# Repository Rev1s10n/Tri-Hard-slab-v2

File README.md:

# Tri-Hard slab v2
## **English | [繁體中文](README_zh-TW.md)**
Slim all button controller powered by [GP2040-CE](https://gp2040-ce.info/) firmware (v0.7.5), with custom 15 buttons layout mainly for Street Fighter 6 and upcoming games that may support additional keybinding.

Mainly inspired by [Egg On Rice Controller](https://github.com/b1nc/Egg-On-Rice-Controller) by [b1nc](https://github.com/b1nc), [Mille-feuille](https://pomegd.booth.pm/items/2685530) by [ぽめ](https://twitter.com/pomegd) and [BridgeBoard](https://bridgeshop.booth.pm/items/4869470) by [立川 Bridge](https://twitter.com/GBB_tachikawa).

The design is heavily based on [flatbox](https://github.com/jfedor2/flatbox) rev4 by [jfdeor2](https://github.com/jfedor2) and [USB Passthrough Board](https://github.com/OpenStickCommunity/Hardware/tree/main/USB%20Passthrough%20Board) by [TheTrain](https://github.com/TheTrainGoes) and [Lucipher](https://github.com/arntsonl), which is licensed under [CC BY 4.0](https://creativecommons.org/licenses/by/4.0/).

## Key features and specs
- Dimensions: 270x157x15.6mm, with additional foam pad (for better grip on lap) at the bottom added 4mm so the total height is around 20mm.
- Weights: around 800g.
- Laser-cut arcylic sheets for enclosure, with strap holes on the top.
- Main key switches: Kailh low profile Choc v2 red, with hot swap sockets and Punk Workshop's key caps.
- 1 RGB LED for each key, with additional 4 RGB LEDs for player number indication (XInput only).
- USB Type-C connector, and additional USB Type-A for PS passthrough authentication.
- 1.3 inches OLED display for various info.
- 3 slide switches on the right side for focus mode, SOCD mode and LS / RS / DP change in real-time.

Some close up photo for each feature:

_Main circuit is heavily based on flatbox with some components replaced due to parts shortage_

_3 tactile switches for your daily stuff and the display on the top left, there's additional slide switch for display pin switch (GND / VCC)_

_All slide switches on the right hand side, they sit flush with the enclosure but still can be reach easily_

_It's nice to have but it's only for XInput mode_

_PS5 ready, I guess_

## Production files

_A quick 3D render I did while waiting for acrylic layers_

You can simply download all production files via Hardware files folder, and utilize services like JLCPCB (which is what I did in this case) to order the board. As for the arcrylic layers, use all dxf files and order 1 for each with the exact height mentioned on the filename for optimal result.
To refine it further, send the step files to vendor to ask them to do either fillet (round corner) or chamfer for at least the top layer.

## Source files
The Tri-Hard slab v2 is made with Autodesk Fusion 360 and KiCad 7.0.
Everything is under Source files, include a rough Fusion 360 sketch which is the base of all laser-cut dxf files, step file and for KiCad to align things up. There's additional footprints for some parts that is somewhat interchangeable, but you may need to put extra works like rewire some traces or edit edge cuts.

## Assemble and settings

_Layer indication for acrylic_

Besides the PCB and acrylics, you need to order some additional things for the build:
- Kailh low profile switches, obviously, depends on your keycaps, I use v2 specifically as I want to use Punk Workshop's keycap.
- 15 Kailh low profile hotswap socket (for PG1350, which is compatible with PG1353).
- A 1.3 inches OLED display, which you can find pretty much everywhere, usually it's SH1106 driver, make sure to check the pin order and set the pins accordingly with the slide switch next to it.
- 6 M6 sex bolts / Chicago screws with around 14mm length to secure the whole things.

I've compiled a custom firmware with custom button layout for the OLED display and assigned all the GPIO for each keys and switches, which you can find under Firmware and setting files folder, there's a backup setting files as well with some additional RGB LED setting. Here's some GPIO pin mapping info for reference:
|Keys|GPIO|
|-|-|
|Up|14|
|Down|12|
|Left|11|
|Right|13|
|B1/1K/A/Circle|18|
|B2/2K/B/Cross|19|
|B3/1P/X/Square|15|
|B4/2P/Y/Triangle|16|
|L1/4P/LB|21|
|R1/3P/RB|17|
|L2/4K/LT|22|
|R2/3K/RT|20|
|S1/Select/Back|6|
|S2/Start|8|
|L3/LS|10|
|R3/RS|9|
|A1/Home/Guide|7|
|A2/Touch|24|

Additionally here's the GPIO and some other settings for other features and addons:
|Features|GPIO and index|
|-|-|
|RGB LED Data Pin|3|
|Player LEDs|starting from 15 to 18|
|Display SDA|4|
|Display SCL|5|
|Joystick Selection Slider Pin 1|26|
|Joystick Selection Slider Pin 2|25|
|SOCD Cleaning Mode Selection Slider Pin 1|28|
|SOCD Cleaning Mode Selection Slider Pin 2|27|
|PS Passthrough D+|1|
|PS Passthrough D-|2 (automactically selected)|
|Focus Mode Pin|29|

When it's done, to access web configurator again, just hold S2/Start (GPIO8) which is located on the top left and connect to the PC.

## Custom artwork

You can download the PSD file and dxf drawing reference in Custom artwork template folder for top panel.
Print it out and insert the artwork between 01 and 02 acrylic layers.

## Attribution
You're free to use this design as long as you credit to this page.
[Licensed under CC BY 4.0](https://creativecommons.org/licenses/by/4.0/)

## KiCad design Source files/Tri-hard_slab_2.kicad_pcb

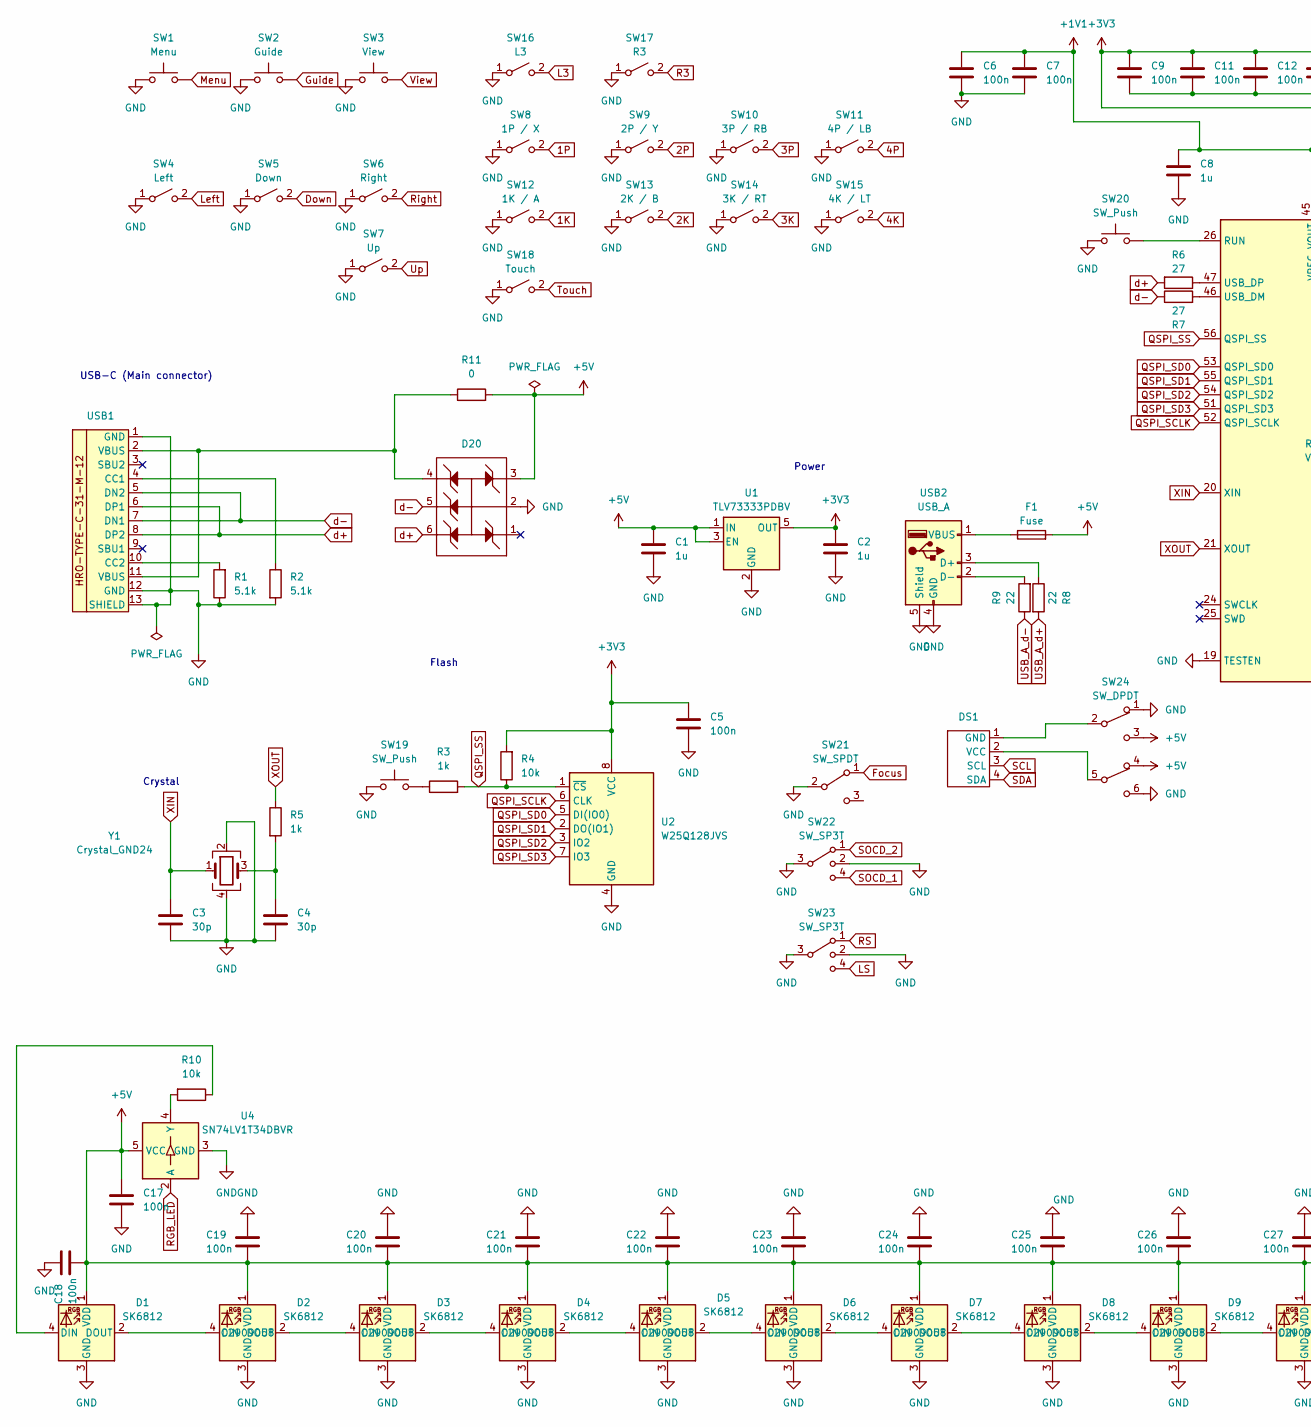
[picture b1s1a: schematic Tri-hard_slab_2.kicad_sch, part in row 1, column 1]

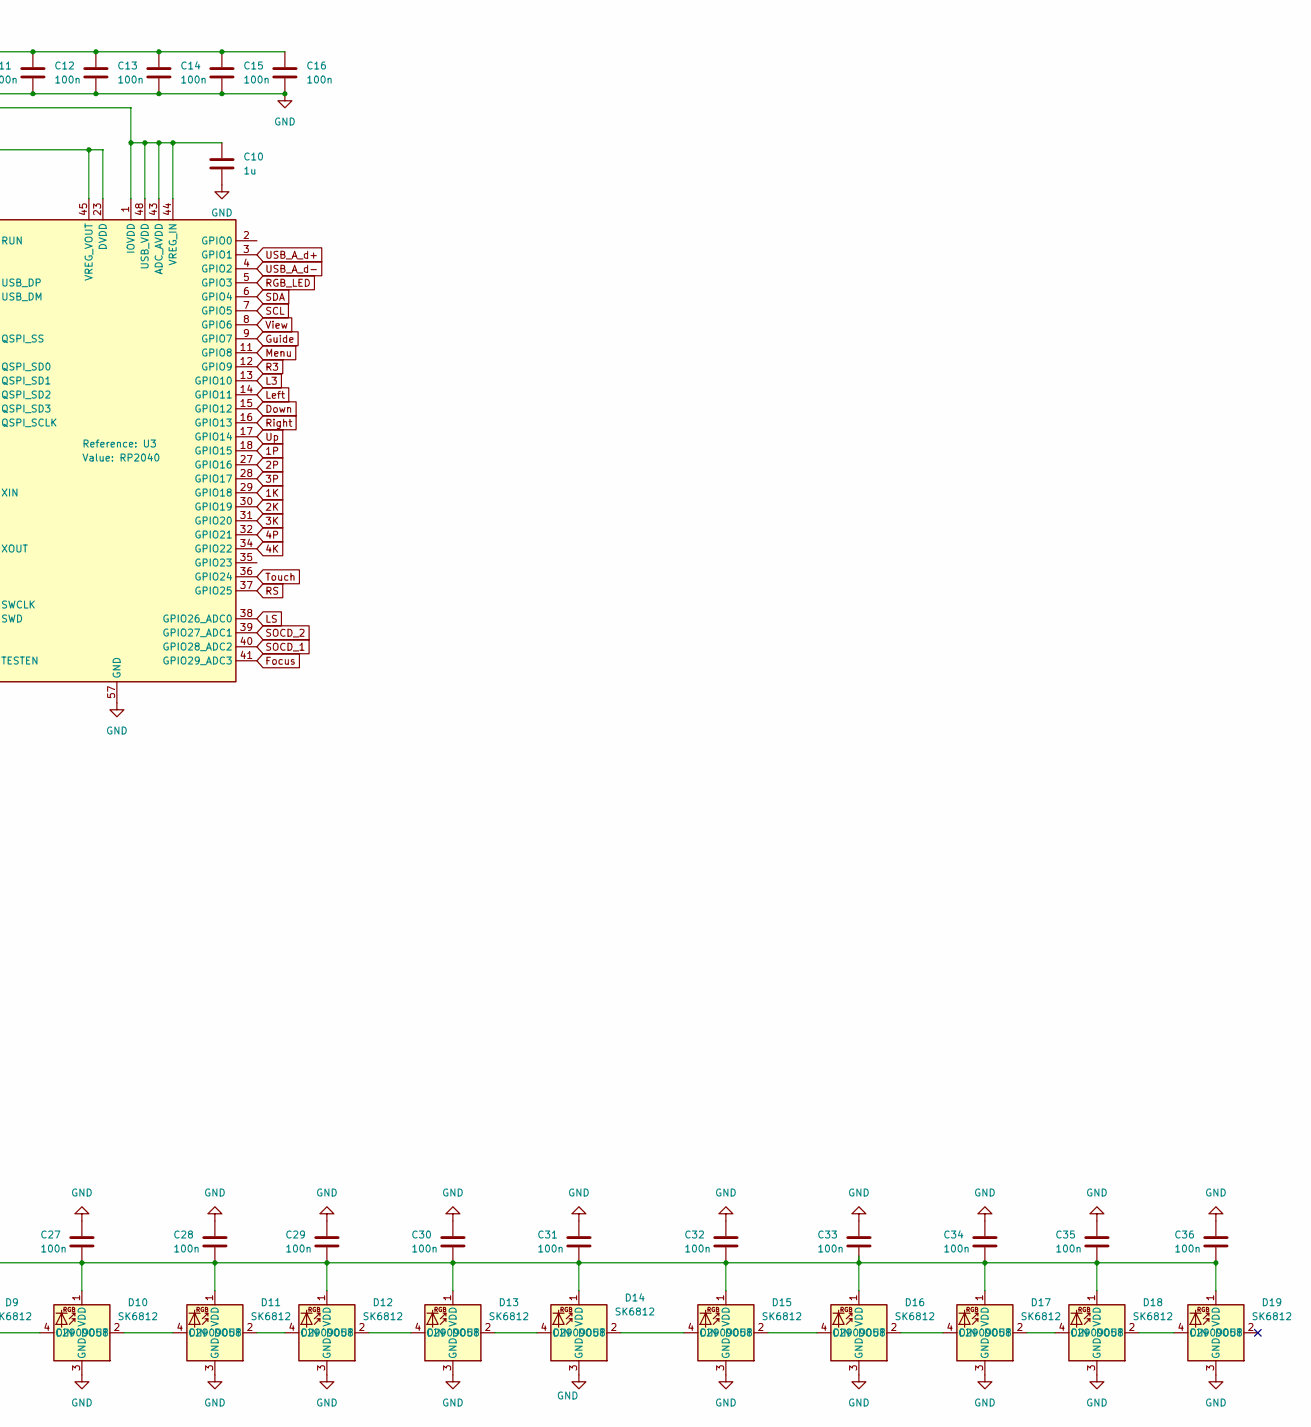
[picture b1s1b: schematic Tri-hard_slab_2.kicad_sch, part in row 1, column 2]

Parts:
C1, C2, C8, C10: 1u; C_0402_1005Metric; LCSC C52923
C3, C4: 30p; C_0402_1005Metric; LCSC C159804
C5, C6, C7, C9, C11, C12, C13, C14, C15, C16, C17, C18, C19, C20, C21, C22, C23, C24, C25, C26, C27, C28, C29, C30, C31, C32, C33, C34, C35, C36: 100n; C_0402_1005Metric; LCSC C1525
D1, D2, D3, D4, D5, D6, D7, D8, D9, D10, D11, D12, D13, D14, D15, D16, D17, D18, D19: SK6812; SK6812-EC20; LCSC C2909058
D20: SOT-363_SC-70-6; LCSC C15879
DS1: 368030501246
F1: Fuse; Fuse_0805_2012Metric; LCSC C116170
R1, R2: 5.1k; R_0402_1005Metric; LCSC C25905
R3, R5: 1k; R_0402_1005Metric; LCSC C11702
R4, R10: 10k; R_0402_1005Metric; LCSC C25744
R6, R7: 27; R_0402_1005Metric; LCSC C138021
R8, R9: 22; R_0603_1608Metric; LCSC C23345
R11: 0; R_0402_1005Metric; LCSC C17168
SW1: Menu; TS-1003S-09526; LCSC C455228
SW2: Guide; TS-1003S-09526; LCSC C455228
SW3: View; TS-1003S-09526; LCSC C455228
SW4: Left; SW_Hotswap_Kailh_Choc_V1V2
SW5: Down; SW_Hotswap_Kailh_Choc_V1V2
SW6: Right; SW_Hotswap_Kailh_Choc_V1V2
SW7: Up; SW_Hotswap_Kailh_Choc_V1V2
SW8: 1P / X; SW_Hotswap_Kailh_Choc_V1V2
SW9: 2P / Y; SW_Hotswap_Kailh_Choc_V1V2
SW10: 3P / RB; SW_Hotswap_Kailh_Choc_V1V2
SW11: 4P / LB; SW_Hotswap_Kailh_Choc_V1V2
SW12: 1K / A; SW_Hotswap_Kailh_Choc_V1V2
SW13: 2K / B; SW_Hotswap_Kailh_Choc_V1V2
SW14: 3K / RT; SW_Hotswap_Kailh_Choc_V1V2
SW15: 4K / LT; SW_Hotswap_Kailh_Choc_V1V2
SW16: L3; SW_Hotswap_Kailh_Choc_V1V2
SW17: R3; SW_Hotswap_Kailh_Choc_V1V2
SW18: Touch; SW_Hotswap_Kailh_Choc_V1V2
SW19, SW20: SW_Push; SKRAAKE010; LCSC C115354
SW21: SW_SPDT; K3-1245D-F1; LCSC C145859
SW22, SW23: SW_SP3T; K3-1346E-F1; LCSC C502339
SW24: SW_DPDT; SSSS820101; LCSC C97434
U1: TLV73333PDBV; SOT-23-5; LCSC C134139
U2: W25Q128JVS; SOIC-8_5.23x5.23mm_P1.27mm
U3: RP2040; RP2040-QFN-56; LCSC C2040
U4: SN74LV1T34DBVR; SOT-23-5; LCSC C100024
USB1: USB_C_Receptacle_HRO_TYPE-C-31-M-12; LCSC C165948
USB2: USB_A; U-A-24DD-W-16; LCSC C2689981
Y1: Crystal_GND24; Crystal_SMD_3225-4Pin_3.2x2.5mm; LCSC C9002

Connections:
1K: SW12.2 (B), U3.29 (GPIO18)
1P: SW8.2 (B), U3.18 (GPIO15)
2K: SW13.2 (B), U3.30 (GPIO19)
2P: SW9.2 (B), U3.27 (GPIO16)
3K: SW14.2 (B), U3.31 (GPIO20)
3P: SW10.2 (B), U3.28 (GPIO17)
4K: SW15.2 (B), U3.34 (GPIO22)
4P: SW11.2 (B), U3.32 (GPIO21)
+1V1: C6.1, C7.1, C8.1, U3.23 (DVDD), U3.45 (VREG_VOUT), U3.50 (DVDD)
+3V3: C2.1, C5.1, C9.1, C10.1, C11.1, C12.1, C13.1, C14.1, C15.1, C16.1, R4.2, U1.5 (OUT), U2.8 (VCC), U3.1 (IOVDD), U3.10 (IOVDD), U3.22 (IOVDD), U3.33 (IOVDD), U3.42 (IOVDD), U3.43 (ADC_AVDD), U3.44 (VREG_IN), U3.48 (USB_VDD), U3.49 (IOVDD)
+5V: C1.1, C17.1, C18.1, C19.1, C20.1, C21.1, C22.1, C23.1, C24.1, C25.1, C26.1, C27.1, C28.1, C29.1, C30.1, C31.1, C32.1, C33.1, C34.1, C35.1, C36.1, D1.1 (VDD), D2.1 (VDD), D3.1 (VDD), D4.1 (VDD), D5.1 (VDD), D6.1 (VDD), D7.1 (VDD), D8.1 (VDD), D9.1 (VDD), D10.1 (VDD), D11.1 (VDD), D12.1 (VDD), D13.1 (VDD), D14.1 (VDD), D15.1 (VDD), D16.1 (VDD), D17.1 (VDD), D18.1 (VDD), D19.1 (VDD), D20.3, F1.2, R11.2, SW24.3 (C), SW24.4 (A), U1.1 (IN), U1.3 (EN), U4.5 (VCC)
Down: SW5.2 (B), U3.15 (GPIO12)
Focus: SW21.1 (A), U3.41 (GPIO29_ADC3)
GND: C1.2, C2.2, C3.2, C4.2, C5.2, C6.2, C7.2, C8.2, C9.2, C10.2, C11.2, C12.2, C13.2, C14.2, C15.2, C16.2, C17.2, C18.2, C19.2, C20.2, C21.2, C22.2, C23.2, C24.2, C25.2, C26.2, C27.2, C28.2, C29.2, C30.2, C31.2, C32.2, C33.2, C34.2, C35.2, C36.2, D1.3 (GND), D2.3 (GND), D3.3 (GND), D4.3 (GND), D5.3 (GND), D6.3 (GND), D7.3 (GND), D8.3 (GND), D9.3 (GND), D10.3 (GND), D11.3 (GND), D12.3 (GND), D13.3 (GND), D14.3 (GND), D15.3 (GND), D16.3 (GND), D17.3 (GND), D18.3 (GND), D19.3 (GND), D20.2, R1.1, R2.2, SW1.1, SW2.1, SW3.1, SW4.1 (A), SW5.1 (A), SW6.1 (A), SW7.1 (A), SW8.1 (A), SW9.1 (A), SW10.1 (A), SW11.1 (A), SW12.1 (A), SW13.1 (A), SW14.1 (A), SW15.1 (A), SW16.1 (A), SW17.1 (A), SW18.1 (A), SW19.1, SW20.1, SW21.2 (B), SW22.2, SW22.3, SW23.2, SW23.3, SW24.1 (A), SW24.6 (C), U1.2 (GND), U2.4 (GND), U3.19 (TESTEN), U3.57 (GND), U4.3 (GND), USB1.1 (GND), USB1.12 (GND), USB1.13 (SHIELD), USB2.4 (GND), USB2.5 (Shield), Y1.2, Y1.4
Guide: SW2.2, U3.9 (GPIO7)
L3: SW16.2 (B), U3.13 (GPIO10)
LS: SW23.4, U3.38 (GPIO26_ADC0)
Left: SW4.2 (B), U3.14 (GPIO11)
Menu: SW1.2, U3.11 (GPIO8)
unnamed: C4.1, R5.2, Y1.3
unnamed: D1.4 (DIN), R10.1
unnamed: D1.2 (DOUT), D2.4 (DIN)
unnamed: D2.2 (DOUT), D3.4 (DIN)
unnamed: D3.2 (DOUT), D4.4 (DIN)
unnamed: D4.2 (DOUT), D5.4 (DIN)
unnamed: D5.2 (DOUT), D6.4 (DIN)
unnamed: D6.2 (DOUT), D7.4 (DIN)
unnamed: D7.2 (DOUT), D8.4 (DIN)
unnamed: D8.2 (DOUT), D9.4 (DIN)
unnamed: D9.2 (DOUT), D10.4 (DIN)
unnamed: D10.2 (DOUT), D11.4 (DIN)
unnamed: D11.2 (DOUT), D12.4 (DIN)
unnamed: D12.2 (DOUT), D13.4 (DIN)
unnamed: D13.2 (DOUT), D14.4 (DIN)
unnamed: D14.2 (DOUT), D15.4 (DIN)
unnamed: D15.2 (DOUT), D16.4 (DIN)
unnamed: D16.2 (DOUT), D17.4 (DIN)
unnamed: D17.2 (DOUT), D18.4 (DIN)
unnamed: D18.2 (DOUT), D19.4 (DIN)
unnamed: D20.4, R11.1, USB1.2 (VBUS), USB1.11 (VBUS)
unnamed: DS1.1 (GND), SW24.2 (B)
unnamed: DS1.2 (VCC), SW24.5 (B)
unnamed: R3.1, SW19.2
unnamed: SW20.2, U3.26 (RUN)
unnamed: R7.2, U3.46 (USB_DM)
unnamed: R6.1, U3.47 (USB_DP)
unnamed: R10.2, U4.4 (Y)
unnamed: R2.1, USB1.4 (CC1)
unnamed: R1.2, USB1.10 (CC2)
unnamed: R8.1, USB2.3 (D+)
unnamed: R9.2, USB2.2 (D-)
unnamed: F1.1, USB2.1 (VBUS)
QSPI_SCLK: U2.6 (CLK), U3.52 (QSPI_SCLK)
QSPI_SD0: U2.5 (DI(IO0)), U3.53 (QSPI_SD0)
QSPI_SD1: U2.2 (DO(IO1)), U3.55 (QSPI_SD1)
QSPI_SD2: U2.3 (IO2), U3.54 (QSPI_SD2)
QSPI_SD3: U2.7 (IO3), U3.51 (QSPI_SD3)
QSPI_SS: R3.2, R4.1, U2.1 (~CS), U3.56 (QSPI_SS)
R3: SW17.2 (B), U3.12 (GPIO9)
RGB_LED: U3.5 (GPIO3), U4.2 (A)
RS: SW23.1, U3.37 (GPIO25)
Right: SW6.2 (B), U3.16 (GPIO13)
SCL: DS1.3 (SCL), U3.7 (GPIO5)
SDA: DS1.4 (SDA), U3.6 (GPIO4)
SOCD_1: SW22.4, U3.40 (GPIO28_ADC2)
SOCD_2: SW22.1, U3.39 (GPIO27_ADC1)
Touch: SW18.2 (B), U3.36 (GPIO24)
USB_A_d+: R8.2, U3.3 (GPIO1)
USB_A_d-: R9.1, U3.4 (GPIO2)
Up: SW7.2 (B), U3.17 (GPIO14)
View: SW3.2, U3.8 (GPIO6)
XIN: C3.1, U3.20 (XIN), Y1.1
XOUT: R5.1, U3.21 (XOUT)
d+: D20.6, R6.2, USB1.6 (DP1), USB1.8 (DP2)
d-: D20.5, R7.1, USB1.5 (DN2), USB1.7 (DN1)

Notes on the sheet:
Crystal
USB-C (Main connector)
Flash
Power

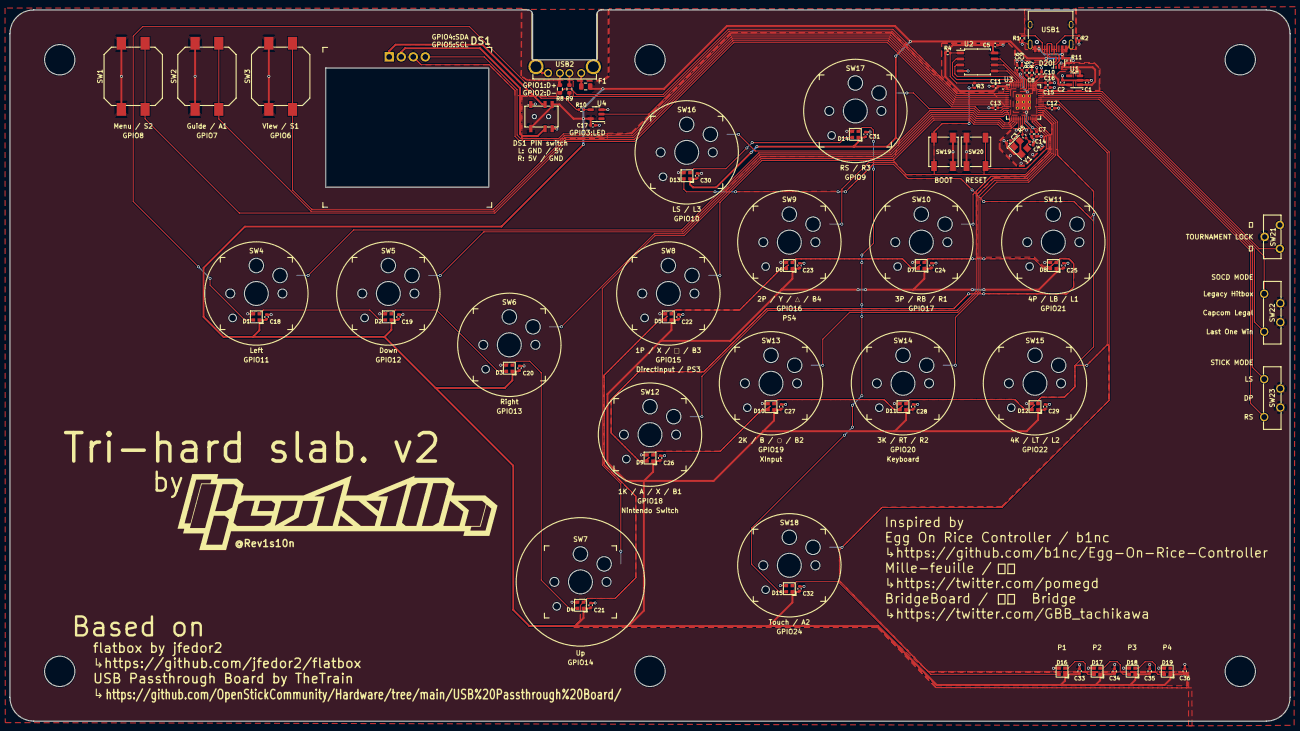
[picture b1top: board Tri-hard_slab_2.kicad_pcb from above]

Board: 2 copper layers, 270.0 x 150.0 mm, 106 parts (0 on the bottom side), 75 nets.

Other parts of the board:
M1, M2, M3, M4, M5, M6: MountingHole_6.4mm_M6

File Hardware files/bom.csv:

Designator,Footprint,Quantity,Value,LCSC Part #
"C1, C10, C2, C8",0402,4,1u,C52923
"C11, C12, C13, C14, C15, C16, C17, C18, C19, C20, C21, C22, C23, C24, C25, C26, C27, C28, C29, C30, C31, C32, C33, C34, C35, C36, C5, C6, C7, C9",0402,30,100n,C1525
"C3, C4",0402,2,30p,C159804
"D1, D10, D11, D12, D13, D14, D15, D16, D17, D18, D19, D2, D3, D4, D5, D6, D7, D8, D9",SK6812-EC20,19,SK6812,C2909058
D20,SOT-363_SC-70-6,1,~,C15879
DS1,368030501246,1,~,
F1,0805,1,Fuse,C116170
"R1, R2",0402,2,5.1k,C25905
"R10, R4",0402,2,10k,C25744
R11,0402,1,0,C17168
"R3, R5",0402,2,1k,C11702
"R6, R7",0402,2,27,C138021
"R8, R9",0603,2,22,C23345
SW1,TS-1003S-09526,1,Menu,C455228
SW10,SW_Hotswap_Kailh_Choc_V1V2,1,3P / RB,
SW11,SW_Hotswap_Kailh_Choc_V1V2,1,4P / LB,
SW12,SW_Hotswap_Kailh_Choc_V1V2,1,1K / A,
SW13,SW_Hotswap_Kailh_Choc_V1V2,1,2K / B,
SW14,SW_Hotswap_Kailh_Choc_V1V2,1,3K / RT,
SW15,SW_Hotswap_Kailh_Choc_V1V2,1,4K / LT,
SW16,SW_Hotswap_Kailh_Choc_V1V2,1,L3,
SW17,SW_Hotswap_Kailh_Choc_V1V2,1,R3,
SW18,SW_Hotswap_Kailh_Choc_V1V2,1,Touch,
"SW19, SW20",SKRAAKE010,2,SW_Push,C115354
SW2,TS-1003S-09526,1,Guide,C455228
SW21,K3-1245D-F1,1,SW_SPDT,C145859
"SW22, SW23",K3-1346E-F1,2,SW_SP3T,C502339
SW24,SSSS820101,1,SW_DPDT,C97434
SW3,TS-1003S-09526,1,View,C455228
SW4,SW_Hotswap_Kailh_Choc_V1V2,1,Left,
SW5,SW_Hotswap_Kailh_Choc_V1V2,1,Down,
SW6,SW_Hotswap_Kailh_Choc_V1V2,1,Right,
SW7,SW_Hotswap_Kailh_Choc_V1V2,1,Up,
SW8,SW_Hotswap_Kailh_Choc_V1V2,1,1P / X,
SW9,SW_Hotswap_Kailh_Choc_V1V2,1,2P / Y,
U1,SOT-23-5,1,TLV73333PDBV,C134139
U2,SOIC-8_5.23x5.23mm_P1.27mm,1,W25Q128JVS,
U3,RP2040-QFN-56,1,RP2040,C2040
U4,SOT-23-5,1,SN74LV1T34DBVR,C100024
USB1,USB_C_Receptacle_HRO_TYPE-C-31-M-12,1,~,C165948
USB2,U-A-24DD-W-16,1,USB_A,C2689981
Y1,Crystal_SMD_3225-4Pin_3.2x2.5mm,1,Crystal_GND24,C9002

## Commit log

2023-10-24 Create gitkeep
2023-10-25 Minor typo fixes.
2023-10-25 Added artwork related description.
2023-10-25 Typo fixes.
2023-10-25 Why there's so many typo omg.
2023-10-25 Update README_zh-TW.md cuz typo again
2023-10-26 Add a comment regarding Fusion 360 source file.
2023-10-26 更新關於 Fusion 360 原始檔的說明
2023-10-28 Update README.md for custom firmware
2023-10-28 更新關於客製韌體的說明
2024-01-25 New firmware with GP2040-CE 0.7.7 release
2024-01-25 Remove old firmware
2024-01-25 remove old firmware setting file
